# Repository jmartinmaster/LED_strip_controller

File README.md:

# LED_strip_controller
ATMEGA328P-PU used as a LED strip controller

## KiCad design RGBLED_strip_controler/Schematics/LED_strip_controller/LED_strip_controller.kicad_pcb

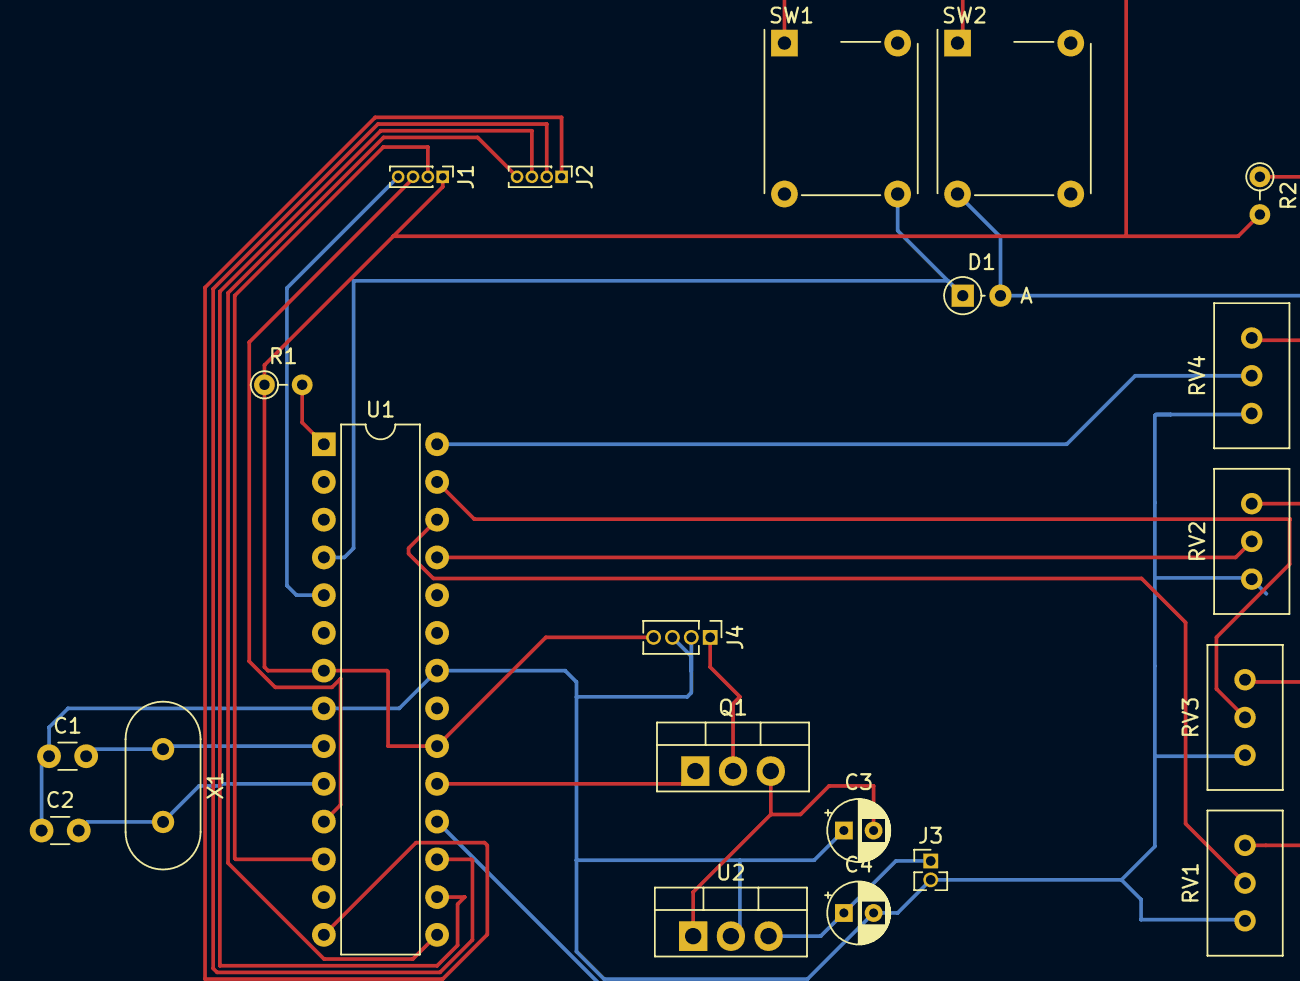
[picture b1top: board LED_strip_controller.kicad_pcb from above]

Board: 2 copper layers, 21 parts (0 on the bottom side), 23 nets.

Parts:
C1, C2: 22pf; C_Disc_D3.0mm_W1.6mm_P2.50mm
C3: 0.22uf; CP_Radial_D4.0mm_P2.00mm
C4: 0.1uf; CP_Radial_D4.0mm_P2.00mm
D1: D; D_DO-34_SOD68_P2.54mm_Vertical_AnodeUp
J1: LEDStrip; PinHeader_1x04_P1.00mm_Vertical
J2: LEDString; PinHeader_1x04_P1.00mm_Vertical
J3: Fountain; PinHeader_1x02_P1.27mm_Vertical
J4: Conn_01x03_Male; PinHeader_1x04_P1.27mm_Vertical
Q1: TIP120; TO-220-3_Vertical
R1: 10K; R_Axial_DIN0204_L3.6mm_D1.6mm_P2.54mm_Vertical
R2: 4.7K; R_Axial_DIN0204_L3.6mm_D1.6mm_P2.54mm_Vertical
RV1, RV2, RV3, RV4: R_POT_TRIM_10K; Potentiometer_Bourns_3296W_Vertical
SW1, SW2: SW_MEC_5G; SW_MEC_5GTH9
U1: ATmega328P-PU; DIP-28_W7.62mm
U2: L7805; TO-220-3_Vertical
X1: 16MHz; Crystal_HC18-U_Vertical

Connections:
+5V: J1.1, J4.4, R1.1, R2.2, SW1.1, SW2.1, U1.7, U1.20
+12: J4.1, Q1.2
GND: C1.1, C2.1, C3.1, C4.2, J3.2, J4.2, J4.3, RV1.3, RV2.3, RV3.3, RV4.3, U1.8, U1.22, U2.2
unnamed: C1.2, U1.9, X1.1
unnamed: C2.2, U1.10, X1.2
unnamed: C3.2, Q1.3, U2.1
unnamed: C4.1, J3.1, U2.3
unnamed: D1.1, SW1.2, U1.4
unnamed: D1.2, SW2.1, U1.18
unnamed: J1.2, U1.12
unnamed: J1.3, U1.11
unnamed: J1.4, U1.5
unnamed: J2.1, U1.14
unnamed: J2.2, U1.17
unnamed: J2.3, U1.16
unnamed: J2.4, U1.15
unnamed: Q1.1, U1.19
unnamed: R1.2, U1.1
unnamed: R2.1, RV1.1, RV2.1, RV3.1, RV4.1
unnamed: RV1.2, U1.26
unnamed: RV2.2, U1.25
unnamed: RV3.2, U1.27
unnamed: RV4.2, U1.28

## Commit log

2020-07-14 Initialization
    seperating code
2020-07-14 Update to 0.6.1 unstable
    this file is being activly changed. this code is to be considered unstable
2020-07-14 Updated annotations
    Added annotations to make it easier to follow the code
2020-07-14 Created version 0.6.2
    Code will begin changing. current code is still unstable
2020-07-15 0.6.2 update UNSTABLE
    adding function to control the house lights and the fountain.
    Fountain has a 7805 attached to 12V line. Need TIP120 to control a 12V signal that is sent to it. TIP120 should connect to D13, Ground, and 12V+.
    Added anotations
2020-07-15 adding forms
    Bug report form added
    Feature request form added
2020-07-16 Updates
    added changelog
    started making schematic so anyone can build it (incomplete)
2020-07-16 Update RGBLED_strip_controler0.6.2.ino
    Fixed a spelling mistake... forgot to make sure it compiled first
2020-07-16 Update unstable
    0.6.2 now works with buttons attached on pins 2 and 14 with a diod to stop button one(attached to 2) from trigering button 2(attached to 12)
    Moving to next version 0.7
2020-07-20 Update to schematic
    Schematic updated(incomplete)
2020-07-20 Updated to new version 0.7
    This version changes alot and is still being worked out. See next version (0.7.2) for better preformance from device.
2020-07-21 Schematic update
    Corrected an error I made.
2020-07-21 Updates to 0.7.2 and changelog
    Changed alot to switch/case and removed some stuff.
    NOT functional yet (7/21/2020 1236)
2020-07-22 Adjusting case/switch
2020-07-22 Updates
    modes 4 and 6 work now
    Button 2 can turn everything "off" (controller is still on and running)
2020-07-22 Update RGBLED_strip_controler0.7.2.ino
    Modes 0,4, and 6 work now. Will be minor changes in a new version to accomidate the controller that is running it
2020-07-25 Update
    Added brightness adjuster. Prepping for some travel so I'm pushing the updates so I can continue working on this
2020-07-25 Update changelog.txt
    Pushed changes for travel
2020-07-31 Rename for Linux compatibility
    The Arduino IDE for Linux doesn't allow a file name with a "." in it so names and change log have been adjusted to reflect this.
    (Eg. 0.7.4 is now 0704)
